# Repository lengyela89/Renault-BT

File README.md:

# Renault-BT
_Version 1.0.0_

The goal of this project is to extend the features of the built-in head units of Renault and Dacia cars (see Supported devices) with the ability to play music from devices via Bluetooth using the A2DP profile.

## Features
- Playing music via bluetooth using the A2DP profile
  - Only one connected device is allowed
  - Audio settings (48kHz, 20bits)
  
## Possible improvements
- Supporting basic commands via AVRCP
  - Volume control (+/-)
  - Play / Pause
  - Next / Previous song
- Supporting built-in dashboard display
  - Show "Bluetooth" text, when HU plays music via bluetooth
- Supporting steering wheel buttons
- Supporting HFP/HSP
  - Answer / Reject call (using HU or steering wheel buttons)

## Supported devices
Built-in head units with "Tuner List" label

## Notes
- The PCB layout is only created to document how the prototype was built.

## Links
Similar project - https://github.com/Tomasz-Mankowski/MeganeBT <br/>
CDCEmulator project - http://tlcdcemu.sourceforge.net/ <br/>
S/PDIF interface - http://www.hardwarebook.info/S/PDIF <br/>
LCD display - http://monorailc.at/cms/index.php?d=2018/03/17/19/20/30-autoradio-tuner-list-4-ecran-lcd <br/>

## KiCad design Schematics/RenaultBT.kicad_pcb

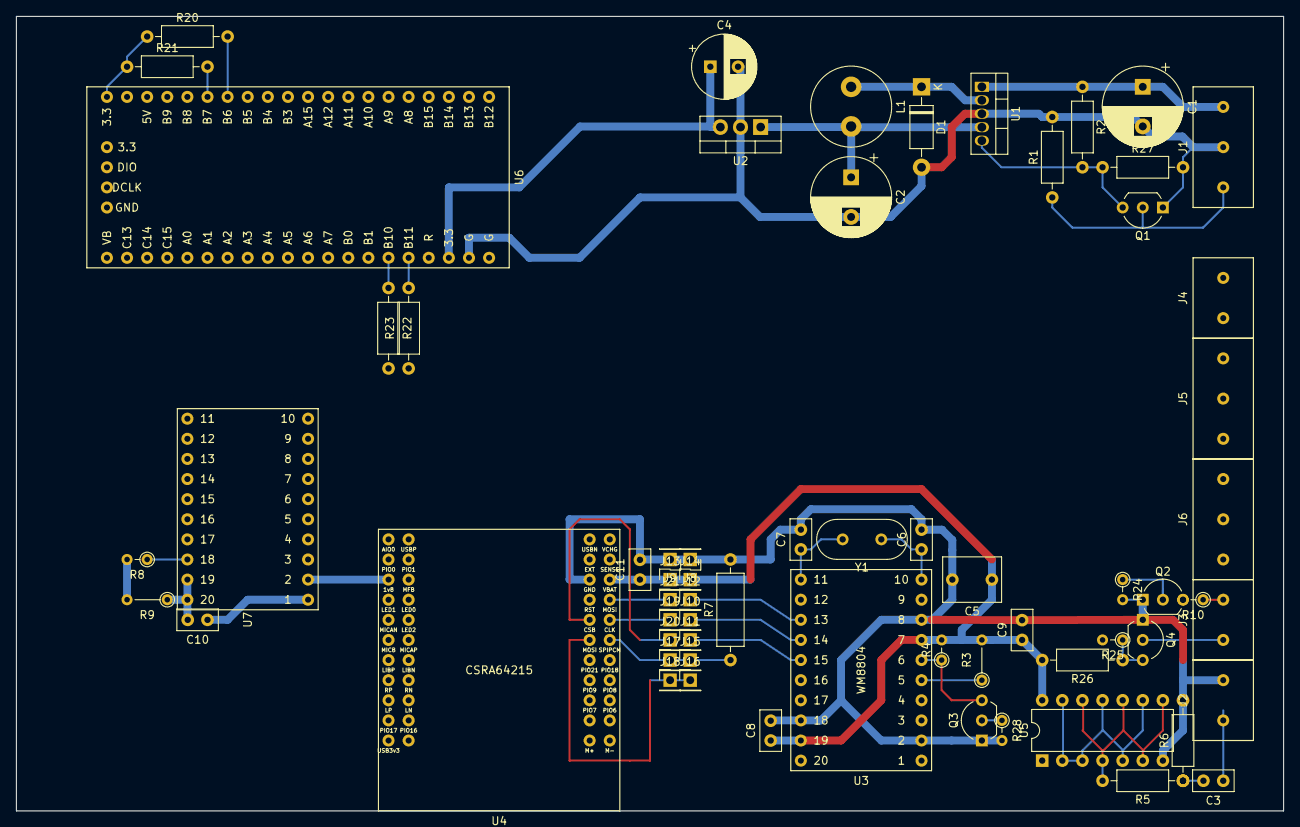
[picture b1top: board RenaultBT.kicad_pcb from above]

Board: 2 copper layers, 160.0 x 100.3 mm, 64 parts (0 on the bottom side), 39 nets.

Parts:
C1: 100uF; CP_Radial_D10.0mm_P5.00mm
C2: 470uF; CP_Radial_D10.0mm_P5.00mm
C3: 0.1u; C_Disc_D5.0mm_W2.5mm_P2.50mm
C4: 470uF; CP_Radial_D8.0mm_P3.50mm
C5: 1uF; C_Rect_L7.2mm_W5.5mm_P5.00mm_FKS2_FKP2_MKS2_MKP2
C6, C7: 15pF; C_Disc_D5.0mm_W2.5mm_P2.50mm
C8, C9, C10, C11: 0.1uF; C_Disc_D5.0mm_W2.5mm_P2.50mm
D1: 1N5819; D_DO-41_SOD81_P10.16mm_Horizontal
J1: PowerSupply; ScrewTerminal_3
J2: SPDIF_Output; ScrewTerminal_2
J3: HU_CDC_Interface; ScrewTerminal_2
J4: Screw_Terminal_01x02; ScrewTerminal_2
J5, J6: Screw_Terminal_01x03; ScrewTerminal_3
J8, J9, J10, J11, J12, J13, J14, J15, J16, J17, J18, J19, J20, J21: Conn_01x01_Male; PinHeader_1x01_P2.54mm_Vertical
L1: 330uH; L_Radial_D10.0mm_P5.00mm_Fastron_07M
Q1, Q2, Q3, Q4: 2N7000; TO-92_Inline_Wide
R1: 10K; R_Axial_DIN0207_L6.3mm_D2.5mm_P10.16mm_Horizontal
R2, R27: 51K; R_Axial_DIN0207_L6.3mm_D2.5mm_P10.16mm_Horizontal
R3: 10k; R_Axial_DIN0204_L3.6mm_D1.6mm_P5.08mm_Vertical
R4, R24, R28: 10K; R_Axial_DIN0204_L3.6mm_D1.6mm_P2.54mm_Vertical
R5: 210; R_Axial_DIN0207_L6.3mm_D2.5mm_P10.16mm_Horizontal
R6: 110; R_Axial_DIN0207_L6.3mm_D2.5mm_P10.16mm_Horizontal
R7: 10k; R_Axial_DIN0309_L9.0mm_D3.2mm_P12.70mm_Horizontal
R8: 330; R_Axial_DIN0204_L3.6mm_D1.6mm_P2.54mm_Vertical
R9: 200K; R_Axial_DIN0204_L3.6mm_D1.6mm_P5.08mm_Vertical
R10: 470; R_Axial_DIN0204_L3.6mm_D1.6mm_P2.54mm_Vertical
R20, R21, R22, R23: 4.7K; R_Axial_DIN0207_L6.3mm_D2.5mm_P10.16mm_Horizontal
R25: 1K; R_Axial_DIN0204_L3.6mm_D1.6mm_P2.54mm_Vertical
R26: 47K; R_Axial_DIN0207_L6.3mm_D2.5mm_P10.16mm_Horizontal
U1: LM2575-5.0BT; TO-220-5_Vertical
U2: LM3940; TO-220-3_Vertical
U3: WM8804; WM8804_Breakout_18mm_x_25mm
U4: CSRA64215
U5: 74HC04; DIP-14_W7.62mm
U6: STM32F103; STM32F103C8T6
U7: GTL2003
Y1: 12Mhz; Crystal_HC49-4H_Vertical

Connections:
/BTModule/3V3: C11.1, J13.1, J14.1, R8.2, R9.2, U4.17
/BTModule/I2S_CLK: J10.1, U3.14, U7.16
/BTModule/I2S_WS: J11.1, U3.15, U7.17
/HU_CDC_InterfaceAdapter/3V3: C4.1, C5.1, C8.1, C9.1, R3.2, R4.2, R26.2, U2.3, U3.7, U3.19, U5.14, U6.38
/HU_CDC_InterfaceAdapter/CDC_RX: R25.2, U6.7
/HU_CDC_InterfaceAdapter/CDC_TX: Q2.2, R24.1, U6.6
/HU_CDC_InterfaceAdapter/HU_RX: J3.2, R10.1
/HU_CDC_InterfaceAdapter/HU_TX: J3.1, Q4.2
/I2SToSPDIF/DGND: C1.2, C2.2, C4.2, C5.2, C6.2, C7.2, C8.2, C9.2, C10.1, C11.2, D1.2, J1.2, J2.2, J8.1, J9.1, Q1.1, Q2.1, Q3.1, Q4.1, R1.2, R6.2, R7.2, R24.2, R27.2, R28.2, U1.3, U2.2, U3.2, U3.8, U3.18, U4.18, U5.7, U6.39, U7.1
/I2SToSPDIF/I2S_SD_IN: J12.1, R8.1, U3.13, U7.18
/I2SToSPDIF/RESETB: Q3.2, R28.1, U6.23
/I2SToSPDIF/SPDIFOutput_buffered/SPDIF_TTL: U3.17, U5.1
/I2SToSPDIF/SPDIF_OUTPUT: C3.1, J2.1
/MainController/I2C1_SCL: R20.2, U3.1, U6.14
/MainController/I2C1_SDA: R21.2, U3.3, U6.15
/MainController/I2C2_SDA: R23.2, U6.36
/MainController/I2S2_SCL: R22.1, U6.35
/PowerSupply/5V: C2.1, L1.2, U1.4, U2.1
/PowerSupply/12V: C1.1, J1.3, R2.1, U1.1
/PowerSupply/HU_ON: J1.1, Q1.2, R1.1
unnamed: C3.2, R5.1, R6.1
unnamed: C6.1, U3.10, Y1.1
unnamed: C7.1, U3.11, Y1.2
unnamed: C10.2, R9.1, U7.19, U7.20
unnamed: D1.1, L1.1, U1.2
unnamed: J15.1, J17.1, R7.1, U4.11
unnamed: J16.1, J18.1, U4.12
unnamed: J19.1, U4.13, U7.5
unnamed: J20.1, U4.14, U7.4
unnamed: J21.1, U4.15, U7.3
unnamed: Q2.3, R10.2
unnamed: Q3.3, R4.1, U3.6
unnamed: Q4.3, R25.1, R26.1
unnamed: R3.1, U3.5
unnamed: R5.2, U5.4, U5.6, U5.8, U5.10, U5.12
unnamed: R20.1, R21.1, R22.2, R23.1, U6.20
unnamed: U4.28, U7.2
unnamed: U5.2, U5.3, U5.5, U5.9, U5.11, U5.13
PWR_ON: Q1.3, R2.2, R27.1, U1.5

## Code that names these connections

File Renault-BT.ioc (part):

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Mcu.Name=STM32F103C(8-B)Tx
Mcu.Package=LQFP48
Mcu.UserName=STM32F103C8Tx
PA10.Mode=Asynchronous
PA10.Signal=USART1_RX
PA13.Mode=Serial_Wire
PA13.Signal=SYS_JTMS-SWDIO
PA14.Mode=Serial_Wire
PA14.Signal=SYS_JTCK-SWCLK
PA9.Mode=Asynchronous
PA9.Signal=USART1_TX
PB10.Mode=I2C
PB10.Signal=I2C2_SCL
PB11.Mode=I2C
PB11.Signal=I2C2_SDA
PB14.Signal=GPIO_Input
PB15.Signal=GPIO_Output
PB6.Mode=I2C
PB6.Signal=I2C1_SCL
PB7.Mode=I2C
PB7.Signal=I2C1_SDA
PB8.Signal=GPIO_Input
PB9.Signal=GPIO_Output
PC13-TAMPER-RTC.GPIOParameters=GPIO_Label
PC13-TAMPER-RTC.GPIO_Label=LED
PC13-TAMPER-RTC.Signal=GPIO_Output
PC14-OSC32_IN.GPIOParameters=GPIO_Label
PC14-OSC32_IN.GPIO_Label=WM8804_RESET
PC14-OSC32_IN.Signal=GPIO_Output
RCC.SYSCLKFreq_VALUE=36000000
RCC.SYSCLKSource=RCC_SYSCLKSOURCE_PLLCLK
board=Renault-BT

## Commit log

2019-02-10 Project is created with initial peripheral settings.
2019-03-30 Added CDC emulator module; reconfigured pinout.
2019-04-24 Added schematics (KiCAD project)
2019-04-24 Added WM8804 library
2019-06-19 Added BT module, HU-CDC interface adapter, I2S to SPDIF converter, SPDIF interface and main controller to the schematics
2019-06-20 Modified power supply
2019-06-21 Fixed library path errors; added edge-cut for PCB; added screw connector to the schematic
2019-06-21 Added foorprint for screw terminals; simplified power supply; PCB partial design
2019-06-23 Fixed library settings; modified PCB design
2019-06-24 Updated PCB design
2019-07-03 Modified PCB design
2019-07-18 Modified power supply schematic and PCB design; added new library for lm3940 IC.
2019-07-23 Modified power supply schematic: changed C4 output capacitor to 470uF
2019-07-31 Updated power supply schematic and PCB design
2019-08-08 Fixed CDC interface schematic; Fixed SPDIF output interface schematic; Added screw terminals; Modified PCB design
2019-08-08 Added C9 bypass capacitor; minor PCB design fixes
2019-08-08 Minor PCB design fixes
2019-08-09 Minor fixes in PCB design
2019-08-12 Added R28 to Q3 between pin 1 and 2; Updated PCB design
2019-10-28 Fixed voltage level issues between BT module and WM8804; fixed CDC Emulator hw interface; modified PCB design
2020-01-12 Updated schematic and PCB design (minor modifications on layout)
2020-01-12 Added initial version of WM8804 library
2020-01-12 Integration of WM8804 to the SW
2020-01-13 Replaced tabs with spaces in WM8804 lib
2020-01-13 Added TODO to the source code
2020-01-19 Code refactoring
    - helper function for WM8804 configuration was added
    - documentation for WM8804 library was added
    - refactoring main.c
2020-01-19 Code formatting
2020-01-24 Fixed separator comments in CDCE and CDCEM
    #5
2020-01-26 Tabs are replaced with spaces in CDCE and CDCEM
    #5
2020-01-26 Created API documentation for CDCE and CDCEM components.
    #5
2020-01-29 Added E_UNKNOWN error code to CDCE.
    E_UNKNOWN error is returned from CDCE_start function if any kind of
    error occured during the execution of the emulator.
    #5
2020-02-02 Configuration files for CSRA64215 are added (original and also the modified version).
    #2
2020-02-02 Renamed original config file to csra64215_config__original.psr and renamed modified config file to csra64215_config__modified.psr.
    Modifications on the original configuration:
    - Device was renamed to RENAULT-BT
    - Audio settings:
    - I2S - Slave operation
    - I2S - Left justified
    - I2S - No delay
2020-02-04 Update Readme.md
    Minor changes on Readme.md
2020-04-13 Added architecture description (Component diagram)
2020-04-13 Modified architecture model
2020-05-04 Added simplified component diagram to describe the connection between the HU and CDC.
2020-05-04 Fixed typo in HU_CDC diagram.
2020-08-25 Exported schematics to PDF and SVG.
2021-02-14 Updated diagrams for the documentation
2021-02-17 Updated diagrams
2021-04-11 Updated components diagram and added simplified component diagram about audio transmission
